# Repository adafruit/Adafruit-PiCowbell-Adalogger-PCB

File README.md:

## Adafruit PiCowbell Adalogger for Pico - MicroSD, RTC & STEMMA QT PCB

<a href="http://www.adafruit.com/products/5703"><br/>
Click here to purchase one from the Adafruit shop</a>

PCB files for the Adafruit PiCowbell Adalogger for Pico - MicroSD, RTC & STEMMA QT. 

Format is EagleCAD schematic and board layout
* https://www.adafruit.com/product/5703

### Description

Ding dong! Hear that? It's the PiCowbell ringing, letting you know that the new Adafruit PiCowbell Adalogger is in stock and ready to assist your Raspberry Pi Pico and Pico W project with handy hardware and datalogging.

The PiCowbell Adalogger is the same size and shape as a Pico and is intended to socket underneath to make your next data logging or data reading project super easy. Micro SD card socket? Yes! STEMMA QT / Qwiic connector for fast I2C? Indeed. Real Time Clock with battery backup for accurate timekeeping? Of course!

Please Note! There are a lot of possible configurations, and we stock various headers depending on how you want to solder and attach. Especially if you want the Pico on top so that the BOOTSEL button and LED are accessible.

1. Use the Pico Stacking Headers if you want to be able to plug into a breadboard or other accessory with sockets.
2. Use the Pico Socket Headers if you want to plug directly in and have a nice solid connection that doesn't have any poking-out-bits.
3. Use the Short Socket Headers for a very slim but pluggable design; note that you'll want to trim down the Pico's headers or use the short plug headers on the Pico to have a skinny sandwich.
4. Solder the PCB directly to the Pico headers - of course, this is very compact and inexpensive, but you won't be able to remove the PiCowbell.

The PiCowbell Adalogger provides you with:

* Right angle JST SH connector for I2C / Stemma QT / Qwiic connection. Provides 3V, GND, IO4 (SDA), and IO5 (SCL)
* MicroSD card holder for adding as much storage as you could possibly want for reading or writing. Connected to SPI pins 16, 18, 19 and card select on 17. Optional card detect line can be connected to pin 15.
* PCF8523 Real Time Clock with CR1220 Coin cell backup for many years of timekeeping. Set the time once using our example sketches and then you can data-log with accurate timestamps. Uses I2C.
* Reset button - Press to restart your program
* Many pads on the Adalogger has a duplicate hole pad next to it for solder-jumpering
* The ground pads have white silkscreen rectangles to easily identify, plus one long ground strip near the reset button
* Gold-plated pads for easy soldering
If using the Philhower Arduino core, the Wire peripheral is already set up to use IO4 and IO5. If using CircuitPython or MicroPython, you'll need to let the code know to look at 4+5 for SDA+SCL pins.

Does not come with a micro SD card or a coin cell battery. A CR1220 coin cell is required to use the RTC battery-backup capabilities! We don't include one by default to make shipping easier for those abroad, but we do stock them, so pick one up or use any CR1220 you have handy.

### License

Adafruit invests time and resources providing this open source design, please support Adafruit and open-source hardware by purchasing products from [Adafruit](https://www.adafruit.com)!

Designed by Limor Fried/Ladyada for Adafruit Industries.

Creative Commons Attribution/Share-Alike, all text above must be included in any redistribution. 
See license.txt for additional details.

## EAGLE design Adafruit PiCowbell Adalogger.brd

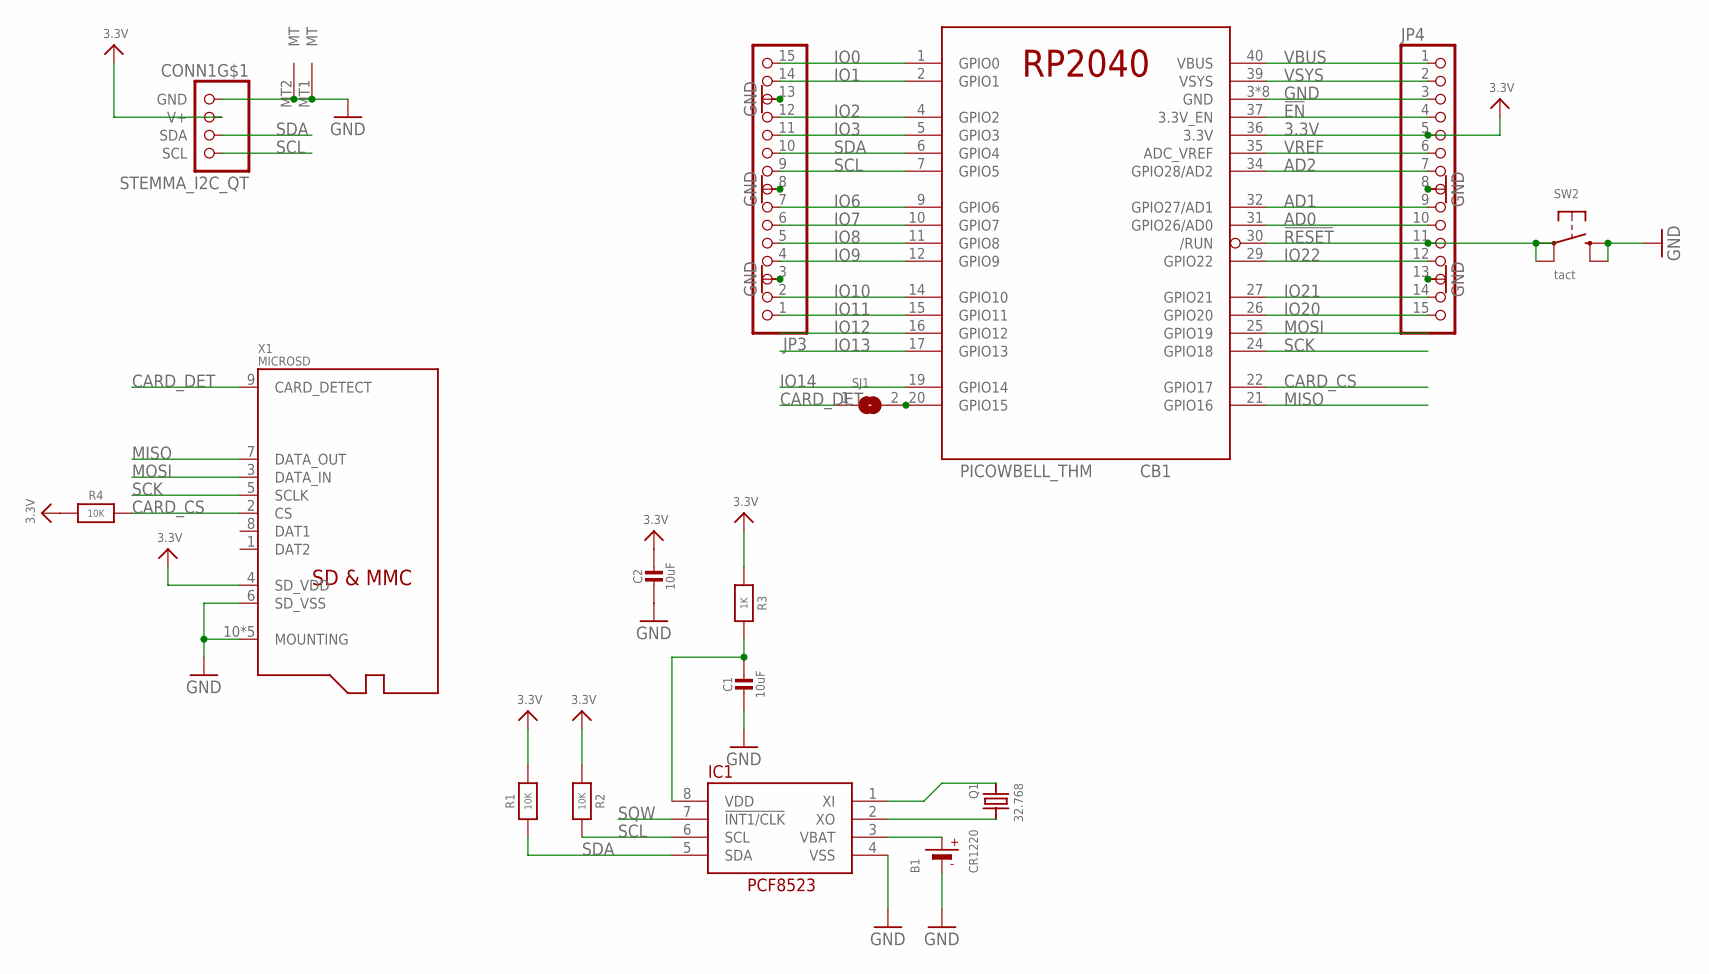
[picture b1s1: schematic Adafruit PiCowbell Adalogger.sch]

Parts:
B1: CR1220; CR1220-2
C1, C2: 10uF; 0805-NO
CB1: PICOWBELL_THM
CONN1: STEMMA_I2C_QT; JST_SH4
IC1: RTC_PCF8523/T; SOIC8_150MIL
JP3, JP4: HEADER-1X15; 1X15_ROUND_70
Q1: 32.768; XTAL3215
R1, R2, R4: 10K; 0603-NO
R3: 1K; 0603-NO
SJ1: SOLDERJUMPER; SOLDERJUMPER_ARROW_NOPASTE
SW2: tact; BTN_RKB2_4.6X2.8
X1: MICROSD; MOLEX_104031-0811

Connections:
3.3V: C2.1, CB1.36 (3.3V), CONN1.2 (V+), JP4.5, R1.2, R2.1, R3.1, R4.1, X1.4 (SD_VDD)
!EN: CB1.37 (3.3V_EN), JP4.4
!RESET: CB1.30 (/RUN), JP4.11, SW2.A, SW2.A' (P1)
AD0: CB1.31 (GPIO26/AD0), JP4.10
AD1: CB1.32 (GPIO27/AD1), JP4.9
AD2: CB1.34 (GPIO28/AD2), JP4.7
CARD_CS: CB1.22 (GPIO17), R4.2, X1.2 (CS)
CARD_DET: SJ1.1, X1.9 (CARD_DETECT)
GND: B1.-, C1.2, C2.2, CB1.3 (GND), CB1.8 (GND), CB1.13 (GND), CB1.18 (GND), CB1.23 (GND), CB1.28 (GND), CB1.33 (GND), CB1.38 (GND), CONN1.1 (GND), CONN1.MT1 (MT), CONN1.MT2 (MT), IC1.4 (VSS), JP3.3, JP3.8, JP3.13, JP4.3, JP4.8, JP4.13, SW2.B (S), SW2.B' (S1), X1.6 (SD_VSS), X1.10 (MOUNTING), X1.G1 (MOUNTING), X1.G2 (MOUNTING), X1.G3 (MOUNTING), X1.G4 (MOUNTING)
IO0: CB1.1 (GPIO0), JP3.15
IO1: CB1.2 (GPIO1), JP3.14
IO2: CB1.4 (GPIO2), JP3.12
IO3: CB1.5 (GPIO3), JP3.11
IO6: CB1.9 (GPIO6), JP3.7
IO7: CB1.10 (GPIO7), JP3.6
IO8: CB1.11 (GPIO8), JP3.5
IO9: CB1.12 (GPIO9), JP3.4
IO10: CB1.14 (GPIO10), JP3.2
IO11: CB1.15 (GPIO11), JP3.1
IO12: CB1.16 (GPIO12)
IO13: CB1.17 (GPIO13)
IO14: CB1.19 (GPIO14)
IO20: CB1.26 (GPIO20), JP4.15
IO21: CB1.27 (GPIO21), JP4.14
IO22: CB1.29 (GPIO22), JP4.12
MISO: CB1.21 (GPIO16), X1.7 (DATA_OUT)
MOSI: CB1.25 (GPIO19), X1.3 (DATA_IN)
unnamed: CB1.20 (GPIO15), SJ1.2
unnamed: C1.1, IC1.8 (VDD), R3.2
unnamed: IC1.1 (XI), Q1.P$1 (1)
unnamed: IC1.2 (XO), Q1.P$2 (2)
SCK: CB1.24 (GPIO18), X1.5 (SCLK)
SCL: CB1.7 (GPIO5), CONN1.4 (SCL), IC1.6 (SCL), JP3.9, R2.2
SDA: CB1.6 (GPIO4), CONN1.3 (SDA), IC1.5 (SDA), JP3.10, R1.1
SQW: IC1.7 (!INT1/CLK)
VBAT: B1.+, IC1.3 (VBAT)
VBUS: CB1.40 (VBUS), JP4.1
VREF: CB1.35 (ADC_VREF), JP4.6
VSYS: CB1.39 (VSYS), JP4.2

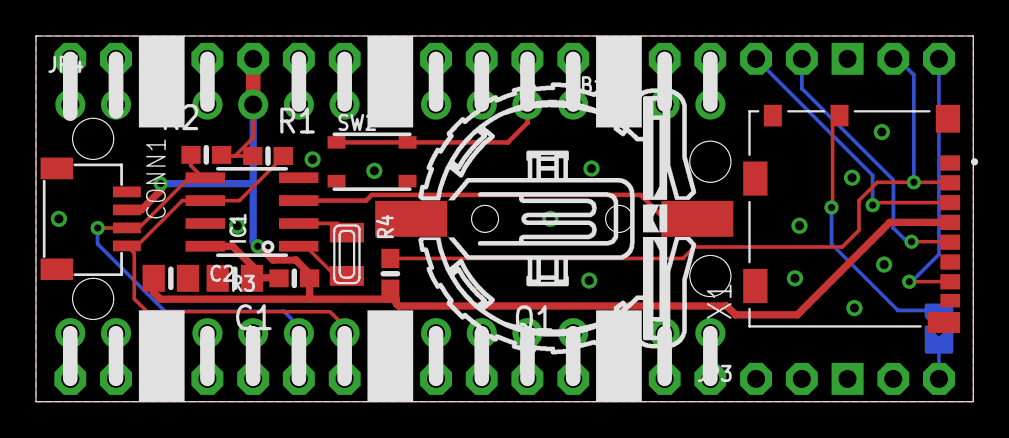
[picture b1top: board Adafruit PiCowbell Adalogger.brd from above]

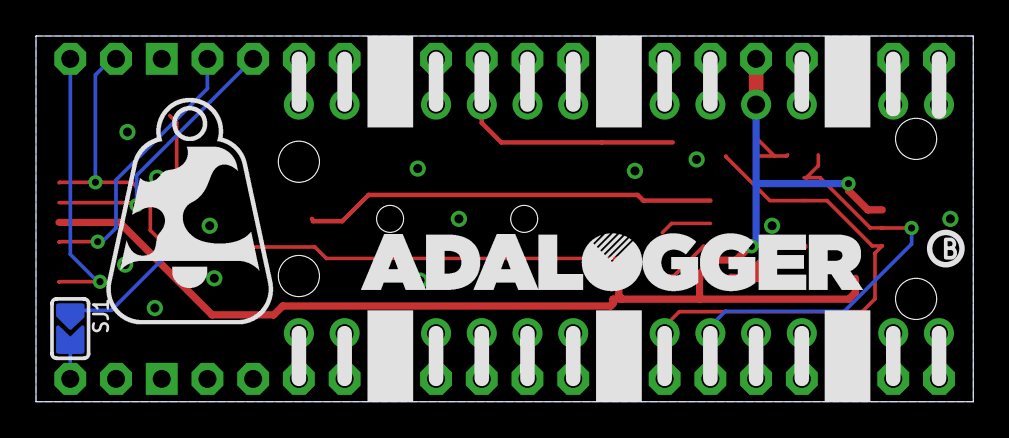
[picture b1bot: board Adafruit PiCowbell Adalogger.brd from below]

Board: 2 copper layers, 52.1 x 20.3 mm, 74 parts (32 on the bottom side), 35 nets.

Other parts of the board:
PLABEL0: PLABEL0
PLABEL1: PLABEL1
PLABEL2: PLABEL2
PLABEL3: PLABEL3
PLABEL4: PLABEL4
PLABEL5: PLABEL5
PLABEL6: PLABEL6
PLABEL7: PLABEL7
PLABEL8: PLABEL8
PLABEL9: PLABEL9
PLABEL10: PLABEL10
PLABEL11: PLABEL11
PLABEL12: PLABEL12
PLABEL13: PLABEL13
PLABEL14: PLABEL14
PLABEL15: PLABEL15
PLABEL16: PLABEL16
PLABEL17: PLABEL17
PLABEL18: PLABEL18
PLABEL19: PLABEL19
PLABEL20: PLABEL20
PLABEL21: PLABEL21
PLABEL22: PLABEL22
PLABEL23: PLABEL23
PLABEL24: PLABEL24
PLABEL25: PLABEL25
PLABEL26: PLABEL26
PLABEL27: PLABEL27
PLABEL30: PLABEL30
PLABEL31: PLABEL31
PLABEL32: PLABEL32
PLABEL33: PLABEL33
PLABEL34: PLABEL34
PLABEL35: PLABEL35
PLABEL36: PLABEL36
PLABEL37: PLABEL37
PLABEL38: PLABEL38
PLABEL39: PLABEL39
PLABEL40: PLABEL40
PLABEL41: PLABEL41
PLABEL42: PLABEL42
PLABEL43: PLABEL43
PLABEL44: PLABEL44
PLABEL45: PLABEL45
PLABEL46: PLABEL46
PLABEL47: PLABEL47
PLABEL48: PLABEL48
PLABEL49: PLABEL49
PLABEL50: PLABEL50
PLABEL51: PLABEL51
PLABEL52: PLABEL52
PLABEL53: PLABEL53
PLABEL54: PLABEL54
PLABEL55: PLABEL55
PLABEL56: PLABEL56
U$10: ADALOGGER_LOGO
U$11: COWBELL_0.5IN
U$12: PCBFEAT-REV-040

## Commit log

2023-03-06 adding cookiecutter output
2023-03-06 updating readme

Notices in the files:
parts and their libraries:
microbuilder: This work is placed in the public domain, and may be freely used for commercial and non-commercial work with the following conditions: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
